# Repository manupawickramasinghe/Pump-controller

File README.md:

# Pump controller
 This is a project that I designed a PCB for, The circuit design was not mine.

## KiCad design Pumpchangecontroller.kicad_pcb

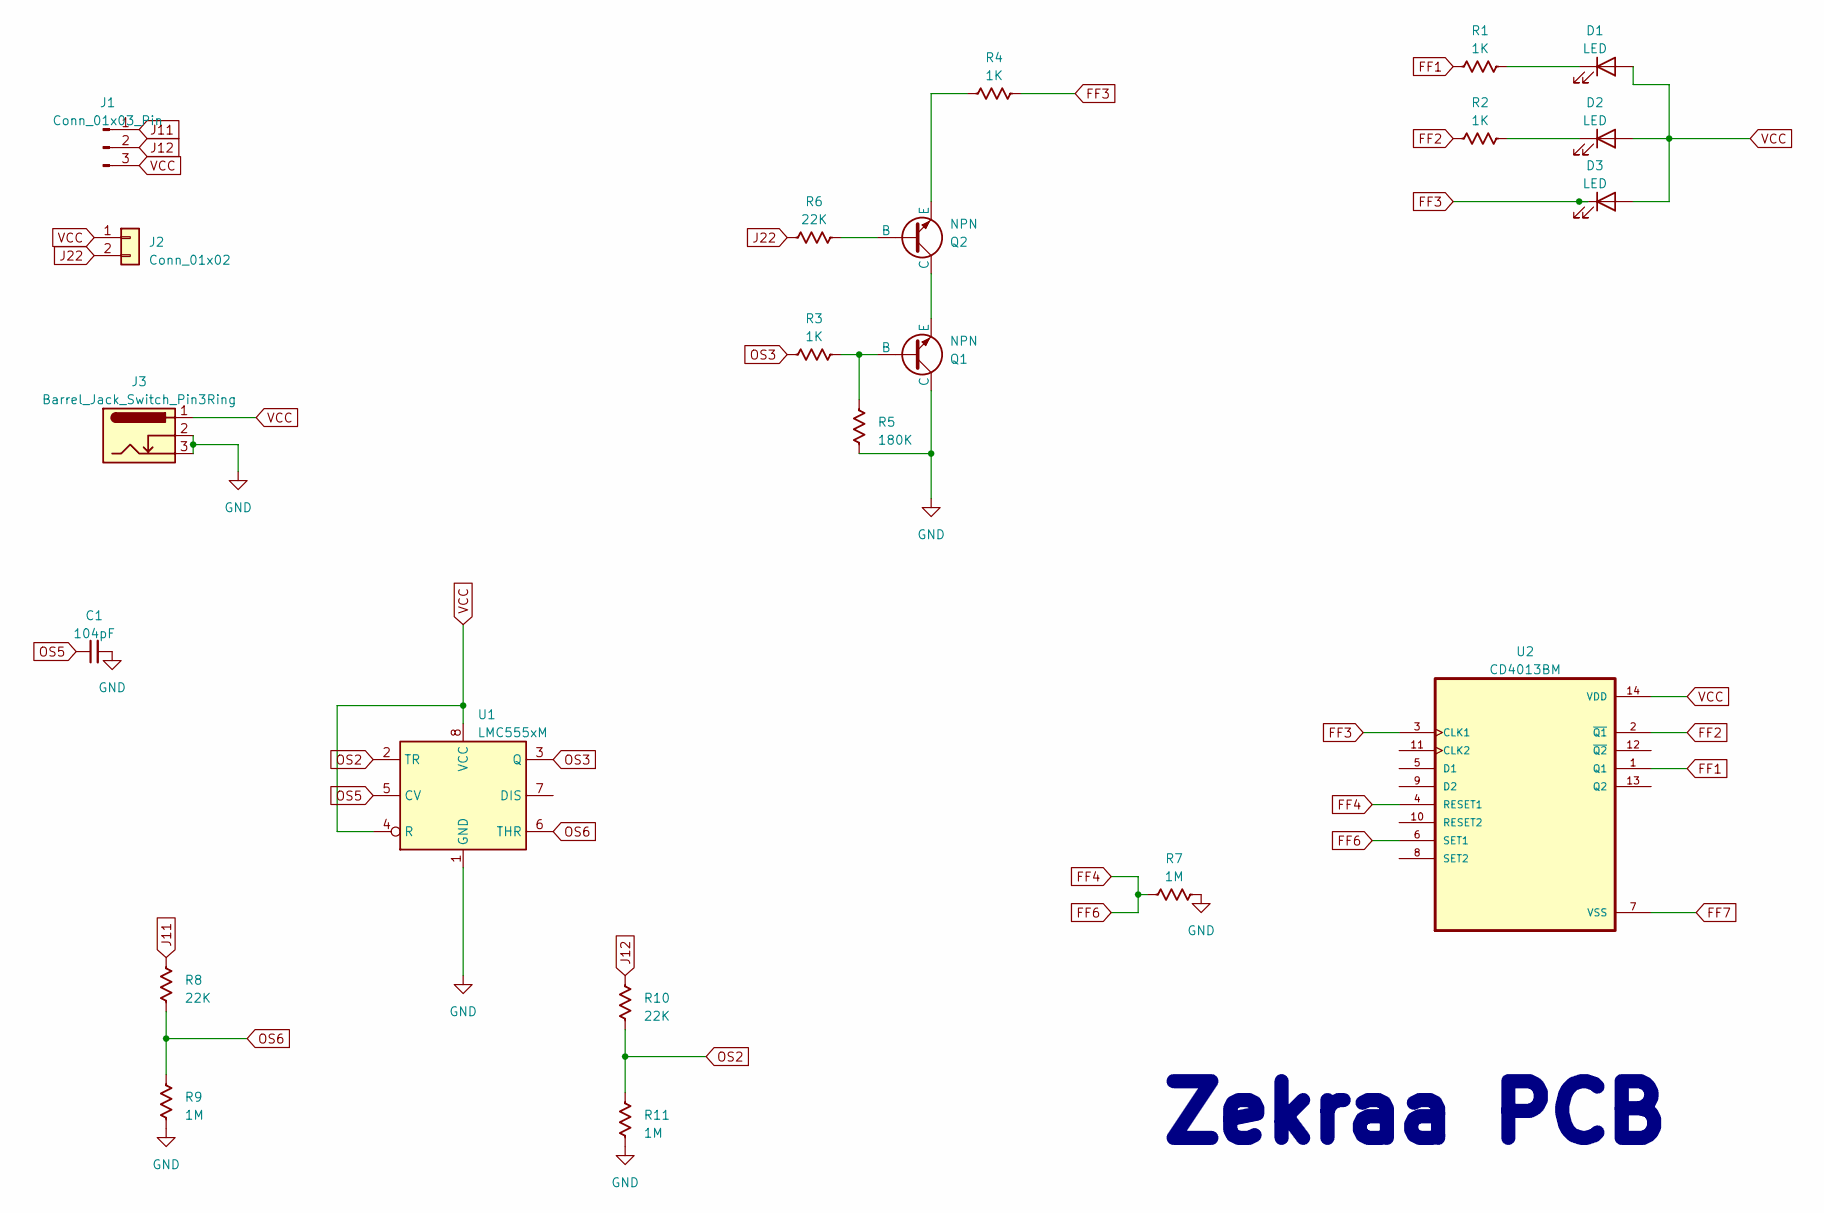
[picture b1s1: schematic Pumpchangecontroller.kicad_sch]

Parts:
C1: C_Generic; CP_Radial_D8.0mm_P5.00mm
D1, D2, D3: LED; LED_D5.0mm
J1: Conn_01x03_Pin; TerminalBlock_Altech_AK300-3_P5.00mm
J2: Conn_01x02; TerminalBlock_Altech_AK300-2_P5.00mm; Part Number 1-0201FBV0T
J3: Barrel_Jack_Switch_Pin3Ring; BarrelJack_Horizontal
Q1, Q2: NPN; TO-92L_ECB
R1, R2, R3, R4: 1K; R_Axial_DIN0411_L9.9mm_D3.6mm_P15.24mm_Horizontal
R5: 180K; R_Axial_DIN0411_L9.9mm_D3.6mm_P15.24mm_Horizontal
R6, R8, R10: 22K; R_Axial_DIN0411_L9.9mm_D3.6mm_P15.24mm_Horizontal
R7, R9, R11: 1M; R_Axial_DIN0411_L9.9mm_D3.6mm_P15.24mm_Horizontal
U1: LMC555xM; DIP-8_W7.62mm
U2: CD4013BM; DIP-14_W7.62mm

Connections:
FF1: R1.2, U2.1 (Q1)
FF2: R2.2, U2.2 (~Q1)
FF3: D3.1 (K), R4.1, U2.3 (CLK1)
FF4: R7.2, U2.4 (RESET1), U2.6 (SET1)
FF7: U2.7 (VSS)
GND: C1.2, J3.2, J3.3, Q1.1 (C), R5.2, R7.1, R9.1, R11.1, U1.1 (GND)
J11: J1.1, R8.2
J12: J1.2, R10.2
J22: J2.2, R6.2
unnamed: D1.1 (K), R1.1
unnamed: D2.1 (K), R2.1
unnamed: Q1.2 (B), R3.1, R5.1
unnamed: Q1.3 (E), Q2.1 (C)
unnamed: Q2.2 (B), R6.1
unnamed: Q2.3 (E), R4.2
OS2: R10.1, R11.2, U1.2 (TR)
OS3: R3.2, U1.3 (Q)
OS5: C1.1, U1.5 (CV)
OS6: R8.1, R9.2, U1.6 (THR)
VCC: D1.2 (A), D2.2 (A), D3.2 (A), J1.3, J2.1, J3.1, U1.4 (R), U1.8 (VCC), U2.14 (VDD)

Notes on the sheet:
Zekraa PCB

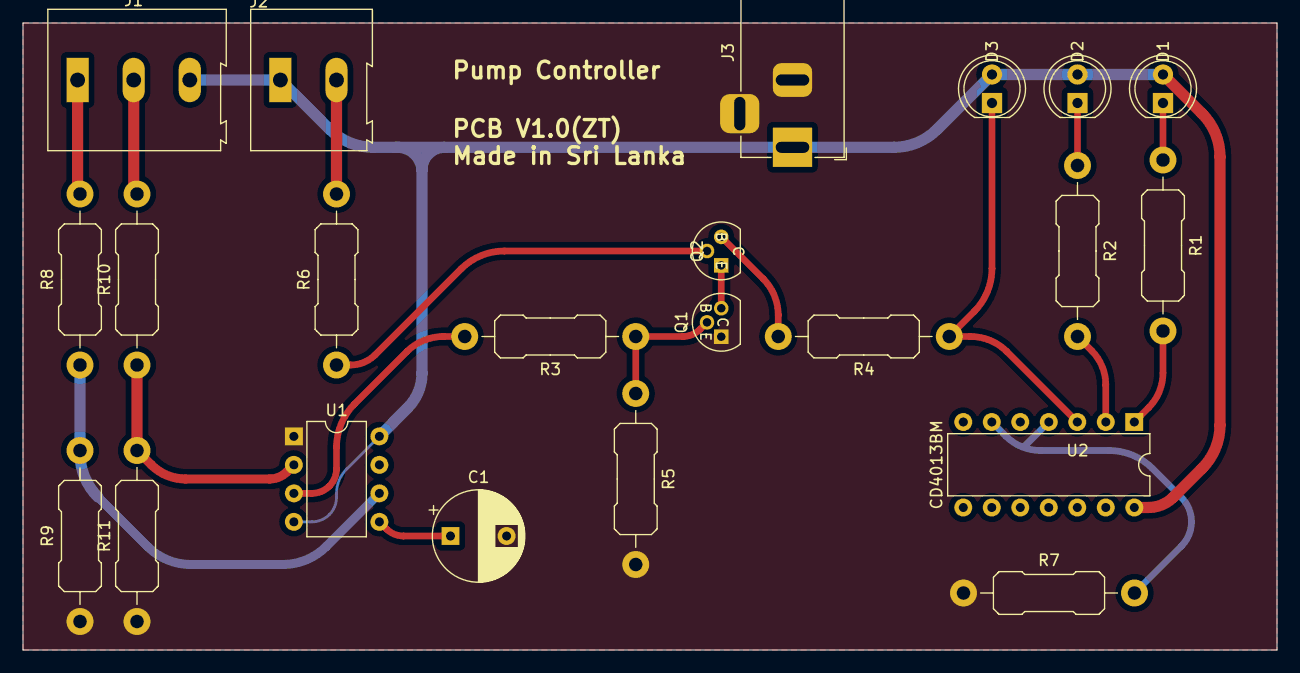
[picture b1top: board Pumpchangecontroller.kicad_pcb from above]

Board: 2 copper layers, 111.8 x 55.9 mm, 22 parts (0 on the bottom side), 19 nets.
